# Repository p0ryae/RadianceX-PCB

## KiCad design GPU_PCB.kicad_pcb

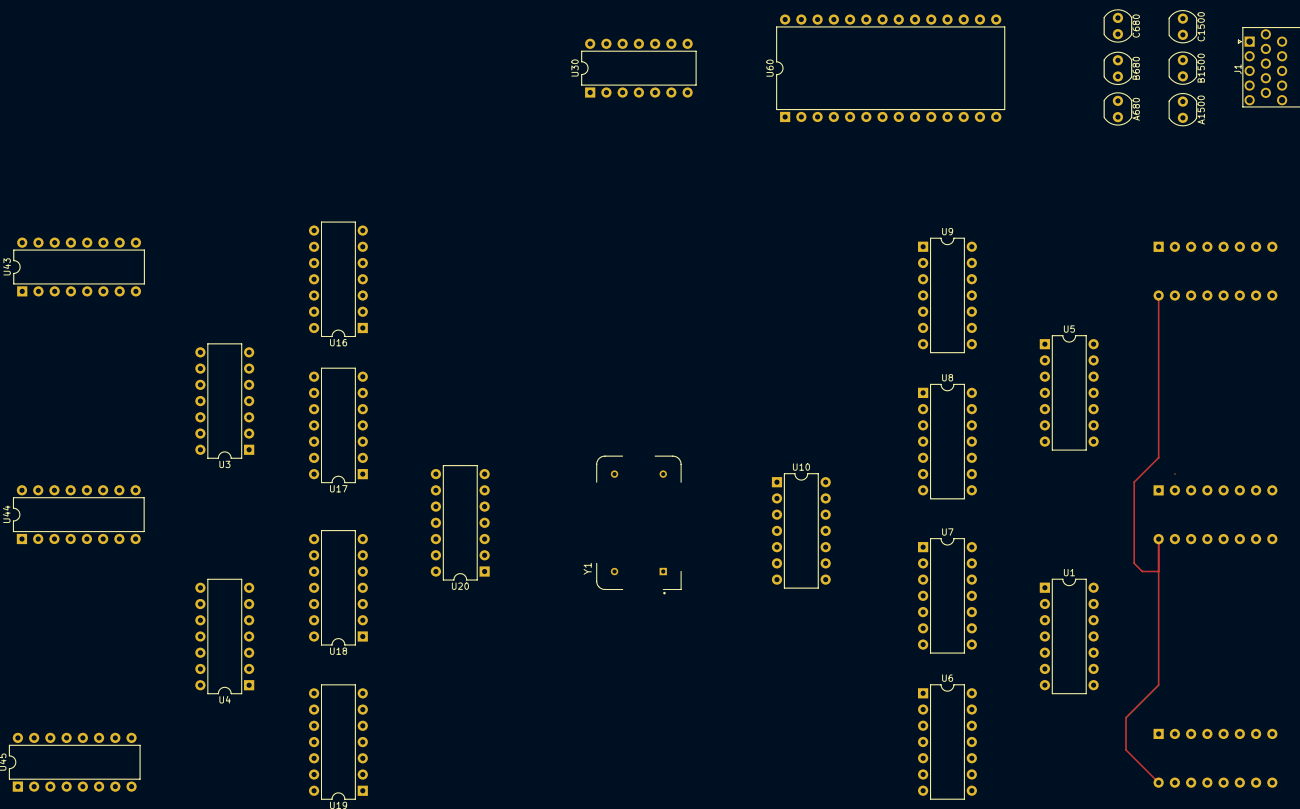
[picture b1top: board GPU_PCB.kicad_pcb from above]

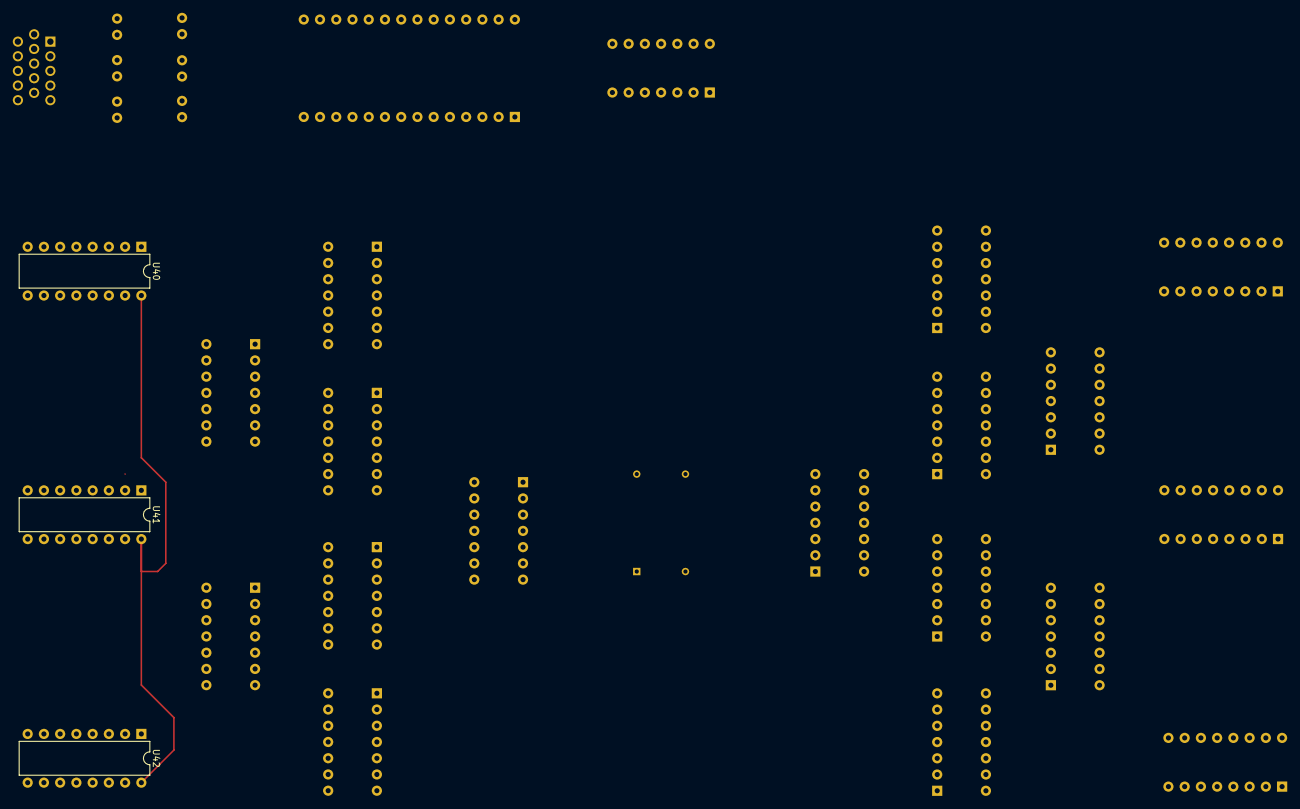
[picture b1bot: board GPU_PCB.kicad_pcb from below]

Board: 2 copper layers, 30 parts (3 on the bottom side), 55 nets.

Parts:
A680: R1; R_LDR_4.9x4.2mm_P2.54mm_Vertical
A1500: R2; R_LDR_4.9x4.2mm_P2.54mm_Vertical
B680: R3; R_LDR_4.9x4.2mm_P2.54mm_Vertical
B1500: R4; R_LDR_4.9x4.2mm_P2.54mm_Vertical
C680: R5; R_LDR_4.9x4.2mm_P2.54mm_Vertical
C1500: R6; R_LDR_4.9x4.2mm_P2.54mm_Vertical
J1: Female_VGA; DSUB-15-HD_Female_Horizontal_P2.29x2.54mm_EdgePinOffset9.40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
U1, U3, U4, U5: 74LS04; DIP-14_W7.62mm
U6, U7, U8, U9, U16, U17, U18, U19: 74LS30; DIP-14_W7.62mm
U10, U20, U30: 74LS00; DIP-14_W7.62mm
U40, U41, U42, U43, U44, U45: 74LS161; DIP-16_W7.62mm
U60: 28C256; DIP-28_W15.24mm
Y1: ECS-100AX; OSC_ECS-100AX-073

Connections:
+5V: U40.7 (CEP), U40.9 (~PE), U40.10 (CET), U40.16 (VCC), U41.7 (CEP), U41.9 (~PE), U41.16 (VCC), U42.7 (CEP), U42.9 (~PE), U42.16 (VCC), U43.7 (CEP), U43.9 (~PE), U43.10 (CET), U43.16 (VCC), U44.7 (CEP), U44.9 (~PE), U44.16 (VCC), U45.7 (CEP), U45.9 (~PE), U45.16 (VCC), U60.27 (~WE), U60.28 (VCC), Y1.14 (+VCC)
/264: U9.8, U10.1, U40.1 (~MR), U40.2 (CP), U41.1 (~MR), U41.2 (CP), U42.1 (~MR), U42.2 (CP), U43.2 (CP), U44.2 (CP), U45.2 (CP), Y1.8 (OUTPUT)
/HBLANK: U10.3, U10.4, U30.1
/HSYNC: J1.13, U10.10, U10.11
/Q0: U1.1, U3.13, U17.2, U18.2, U40.14 (Q0), U43.14 (Q0)
/Q1: U1.3, U3.11, U7.11, U8.11, U40.13 (Q1), U43.13 (Q1), U60.10 (A0)
/Q2: U1.5, U3.9, U18.4, U19.4, U40.12 (Q2), U43.12 (Q2), U60.9 (A1)
/Q3: U1.13, U4.13, U6.2, U9.1, U16.5, U17.5, U18.5, U40.11 (Q3), U43.11 (Q3), U60.3 (A7), U60.8 (A2)
/Q4: U1.11, U7.3, U7.5, U8.3, U16.12, U17.12, U18.12, U41.14 (Q0), U44.14 (Q0), U60.7 (A3), U60.25 (A8)
/Q5: U1.9, U4.11, U8.4, U17.11, U19.6, U41.13 (Q1), U44.13 (Q1), U60.6 (A4), U60.24 (A9)
/Q6: U5.13, U6.5, U8.5, U16.11, U18.11, U41.12 (Q2), U44.12 (Q2), U60.5 (A5), U60.21 (A10)
/Q7: U5.11, U6.6, U7.6, U8.6, U41.11 (Q3), U44.11 (Q3), U60.4 (A6), U60.23 (A11)
/Q8: U5.9, U9.6, U42.14 (Q0), U45.14 (Q0), U60.2 (A12)
/Q9: U16.1, U17.1, U18.1, U19.1, U45.13 (Q1), U60.26 (A13)
/VBLANK: U20.3, U20.4, U30.2
/VSYNC: J1.14, U20.10, U20.11
GND: J1.5, J1.6, J1.7, J1.8, J1.10, U40.8 (GND), U41.8 (GND), U42.8 (GND), U43.8 (GND), U44.8 (GND), U45.8 (GND), U60.1 (A14), U60.14 (GND), U60.20 (~CS), Y1.7 (CASE_GND)
unnamed: A680.1, U60.17 (D5)
unnamed: A1500.1, U60.16 (D4)
unnamed: A680.2, A1500.2, J1.1
unnamed: B680.1, U60.15 (D3)
unnamed: B1500.1, U60.13 (D2)
unnamed: B680.2, B1500.2, J1.2
unnamed: C680.1, U60.12 (D1)
unnamed: C1500.1, U60.11 (D0)
unnamed: C680.2, C1500.2, J1.3
unnamed: U1.2, U6.12, U7.12, U8.12
unnamed: U1.4, U6.11, U9.12
unnamed: U1.6, U6.1, U7.1, U8.1, U9.11
unnamed: U1.8, U6.4, U7.4, U9.3
unnamed: U1.10, U6.3, U9.2
unnamed: U1.12, U7.2, U8.2
unnamed: U5.10, U9.5
unnamed: U5.12, U9.4
unnamed: U10.2, U10.6
unnamed: U6.8, U10.5
unnamed: U7.8, U10.9
unnamed: U10.8, U10.12
unnamed: U8.8, U10.13
unnamed: U3.12, U16.2, U19.2
unnamed: U3.10, U16.3, U17.3, U18.3, U19.3
unnamed: U3.8, U16.4, U17.4
unnamed: U16.6, U17.6, U18.6
unnamed: U16.8, U20.5
unnamed: U17.8, U20.9
unnamed: U18.8, U20.13
unnamed: U4.12, U19.5
unnamed: U19.8, U20.1, U43.1 (~MR), U44.1 (~MR), U45.1 (~MR)
unnamed: U20.2, U20.6
unnamed: U20.8, U20.12
unnamed: U30.3, U60.22 (~OE)
unnamed: U40.15 (TC), U41.10 (CET)
unnamed: U41.15 (TC), U42.10 (CET)
unnamed: U43.15 (TC), U44.10 (CET)
unnamed: U44.15 (TC), U45.10 (CET)

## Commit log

2023-04-02 Just a test
2023-04-02 Small commit
